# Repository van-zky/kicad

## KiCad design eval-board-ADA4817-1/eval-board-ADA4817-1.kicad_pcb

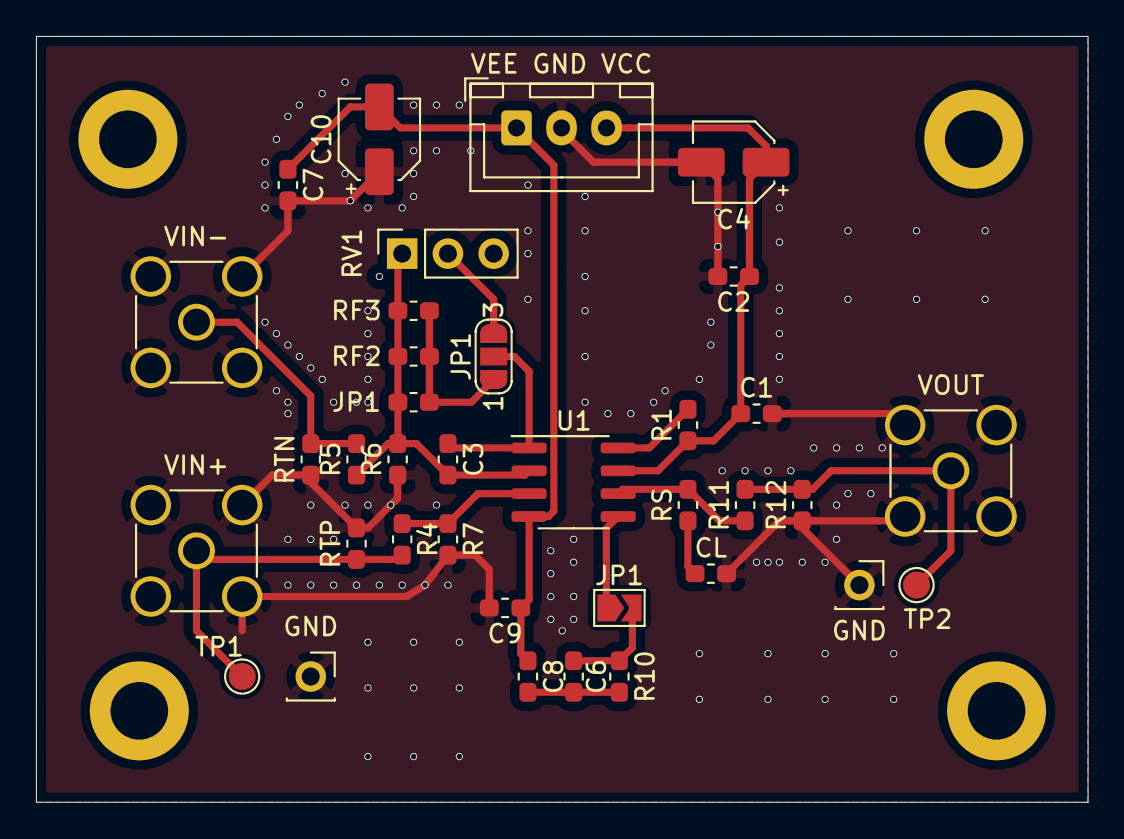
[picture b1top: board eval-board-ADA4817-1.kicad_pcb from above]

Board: 2 copper layers, 58.4 x 42.5 mm, 36 parts (0 on the bottom side), 16 nets.

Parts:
C1, C2, C7, C9: 0.1uF; C_0603_1608Metric_Pad1.05x0.95mm_HandSolder
C3: CF; C_0603_1608Metric_Pad1.05x0.95mm_HandSolder
C4, C10: 10uF; CP_Elec_4x5.4
C6, C8: C; C_0603_1608Metric_Pad1.05x0.95mm_HandSolder
CL: CL; C_0603_1608Metric_Pad1.05x0.95mm_HandSolder
GND: PinSocket_1x01_P2.54mm_Vertical
GND#2: PinSocket_1x01_P2.54mm_Vertical
JP1: SolderJumper-2_P1.3mm_Open_TrianglePad1.0x1.5mm
JP1#2: Jumper_3_Open; SolderJumper-3_P1.3mm_Open_RoundedPad1.0x1.5mm_NumberLabels
JP1#3: R; R_0603_1608Metric_Pad1.05x0.95mm_HandSolder
R1: 1kΩ; R_0603_1608Metric_Pad1.05x0.95mm_HandSolder
R4, R5, R6, R7, R10, R11, R12: R; R_0603_1608Metric_Pad1.05x0.95mm_HandSolder
RF2, RF3: R; R_0603_1608Metric_Pad1.05x0.95mm_HandSolder
RS: RS; R_0603_1608Metric_Pad1.05x0.95mm_HandSolder
RTN: RTN; R_0603_1608Metric_Pad1.05x0.95mm_HandSolder
RTP: RTP; R_0603_1608Metric_Pad1.05x0.95mm_HandSolder
RV1: R_POT; PinSocket_1x03_P2.54mm_Vertical
TP1, TP2: TestPoint_Pad_D1.5mm
U1: ADA4817-1; SOIC-8_3.9x4.9mm_P1.27mm
VEE GND VCC: Conn_01x03_Male; JST_XH_B3B-XH-A_1x03_P2.50mm_Vertical
VIN+: +VIN; SMA_Amphenol_132134-11_Vertical
VIN-: -VIN; SMA_Amphenol_132134-11_Vertical
VOUT: VOUT; SMA_Amphenol_132134-11_Vertical

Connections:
/PD: R1.2, U1.8
/VCC: C1.1, C2.1, C4.1, R1.1, U1.7, VEE GND VCC.3
/VEE: C7.1, C8.1, C9.1, C10.2, U1.4, VEE GND VCC.1
GNDREF: C1.2, C2.2, C4.2, C7.2, C9.2, C10.1, CL.2, GND.1, GND#2.1, R6.1, R7.2, R12.1, RTN.1, RTP.2, VEE GND VCC.2, VIN+.2, VIN-.2, VOUT.2
unnamed: C3.1, JP1#2.2, U1.1
unnamed: C3.2, JP1#3.1, R5.1, R6.2, RF2.1, RF3.2, RV1.1, U1.2
unnamed: CL.1, RS.1
unnamed: C6.1, C8.2, R10.2
unnamed: C6.2, JP1.1, JP1.2, R10.1, U1.5
unnamed: R5.2, RTN.2, VIN-.1
unnamed: R4.2, RTP.1, TP1.1, VIN+.1
unnamed: R11.2, R12.2, TP2.1, VOUT.1
unnamed: JP1#2.1, JP1#3.2, RF2.2, RF3.1
unnamed: JP1#2.3, RV1.2
unnamed: R4.1, R7.1, U1.3
unnamed: R11.1, RS.2, U1.6

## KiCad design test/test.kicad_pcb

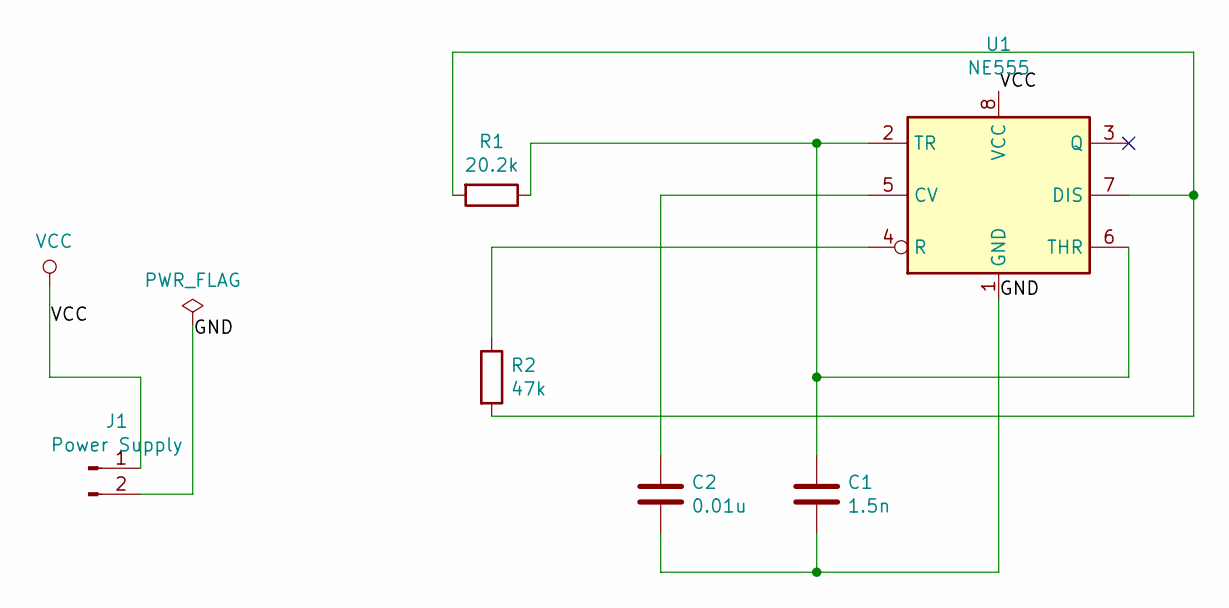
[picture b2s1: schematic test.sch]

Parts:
C1: 1.5n; C_0603_1608Metric
C2: 0.01u; C_0603_1608Metric
J1: Power Supply; PinSocket_1x02_P2.54mm_Horizontal
R1: 20.2k; R_0603_1608Metric
R2: 47k; R_0603_1608Metric
U1: NE555; SOIC-8_3.9x4.9mm_P1.27mm

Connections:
/GND: C1.2, C2.2, J1.2, U1.1 (GND)
unnamed: C1.1, R1.1, U1.2 (TR), U1.6 (THR)
unnamed: C2.1, U1.5 (CV)
unnamed: R1.2, R2.2, U1.7 (DIS)
unnamed: R2.1, U1.4 (R)
VCC: J1.1, U1.8 (VCC)

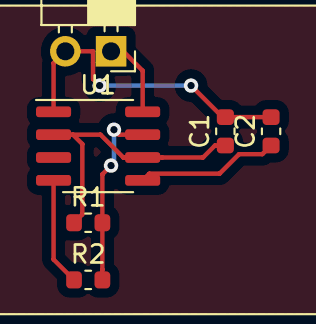
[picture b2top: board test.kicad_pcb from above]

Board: 2 copper layers, 6 parts (0 on the bottom side), 6 nets.

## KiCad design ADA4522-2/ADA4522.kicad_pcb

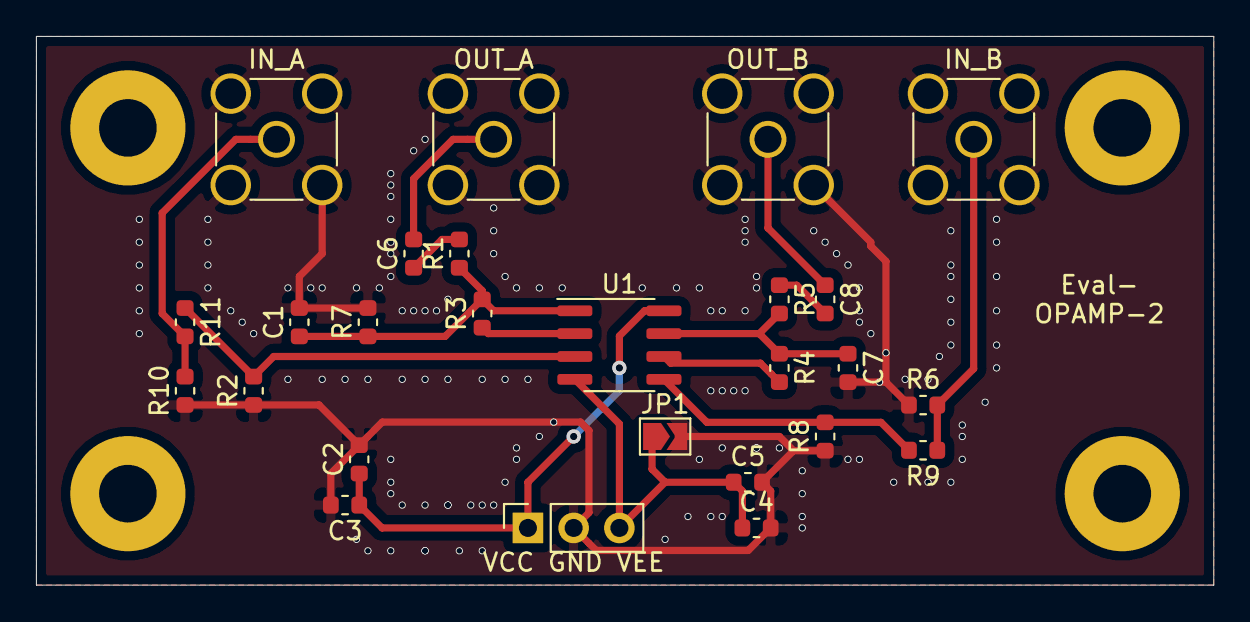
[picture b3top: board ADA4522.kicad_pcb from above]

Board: 2 copper layers, 65.4 x 30.5 mm, 26 parts (0 on the bottom side), 15 nets.

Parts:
C1, C6, C7, C8: 100pF; C_0603_1608Metric
C2, C4: 10uf; C_0603_1608Metric
C3, C5: 0.1uf; C_0603_1608Metric
IN_A: IN_A; SMA_Amphenol_132134-11_Vertical
IN_B: IN_B; SMA_Amphenol_132134-11_Vertical
JP1: SolderJumper-2_P1.3mm_Open_TrianglePad1.0x1.5mm
OUT_A: OUT_A; SMA_Amphenol_132134-11_Vertical
OUT_B: OUT_B; SMA_Amphenol_132134-11_Vertical
R1, R2, R3, R4, R5, R6, R7, R8, R9, R10, R11: R; R_0603_1608Metric
U1: ADA4522-2; SOIC-8_3.9x4.9mm_P1.27mm
VCC GND VEE: Conn_01x03_Male; PinSocket_1x03_P2.54mm_Vertical

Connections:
GND: C1.2, C2.2, C3.2, C4.2, C5.2, C7.2, IN_A.2, IN_B.2, JP1.2, OUT_A.2, OUT_B.2, R2.1, R6.1, R7.2, R8.1, R10.1, VCC GND VEE.2
unnamed: C1.1, R1.1, R3.2, R7.1, U1.1
unnamed: C2.1, C3.1, U1.8, VCC GND VEE.1
unnamed: C4.1, C5.1, JP1.1, U1.4, VCC GND VEE.3
unnamed: C6.1, R1.2
unnamed: C6.2, OUT_A.1
unnamed: C7.1, R4.1, R5.2, U1.7
unnamed: C8.1, OUT_B.1
unnamed: C8.2, R5.1
unnamed: IN_A.1, R10.2, R11.2
unnamed: IN_B.1, R6.2, R9.1
unnamed: R3.1, U1.2
unnamed: R4.2, U1.6
unnamed: R8.2, R9.2, U1.5
unnamed: R2.2, R11.1, U1.3

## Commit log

2019-07-06 update-version
